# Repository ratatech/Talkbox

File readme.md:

# Ratatech Talkbox

This repository contains mainly the PCB design files for the Ratatech Talkbox unit. 

DESCRIPTION WIP.

## Files

* [datasheets](./datasheets) 	Datasheets of some of the components and schematics used in this project.
* [imgs](./imgs) 				Images used in the design and captures or the 3d models/final pcb.
* [kicad](./kicad) 				Main Kicad project directory. Including schematics and pcb.

---

## License

- **[MIT license](http://opensource.org/licenses/mit-license.php)**

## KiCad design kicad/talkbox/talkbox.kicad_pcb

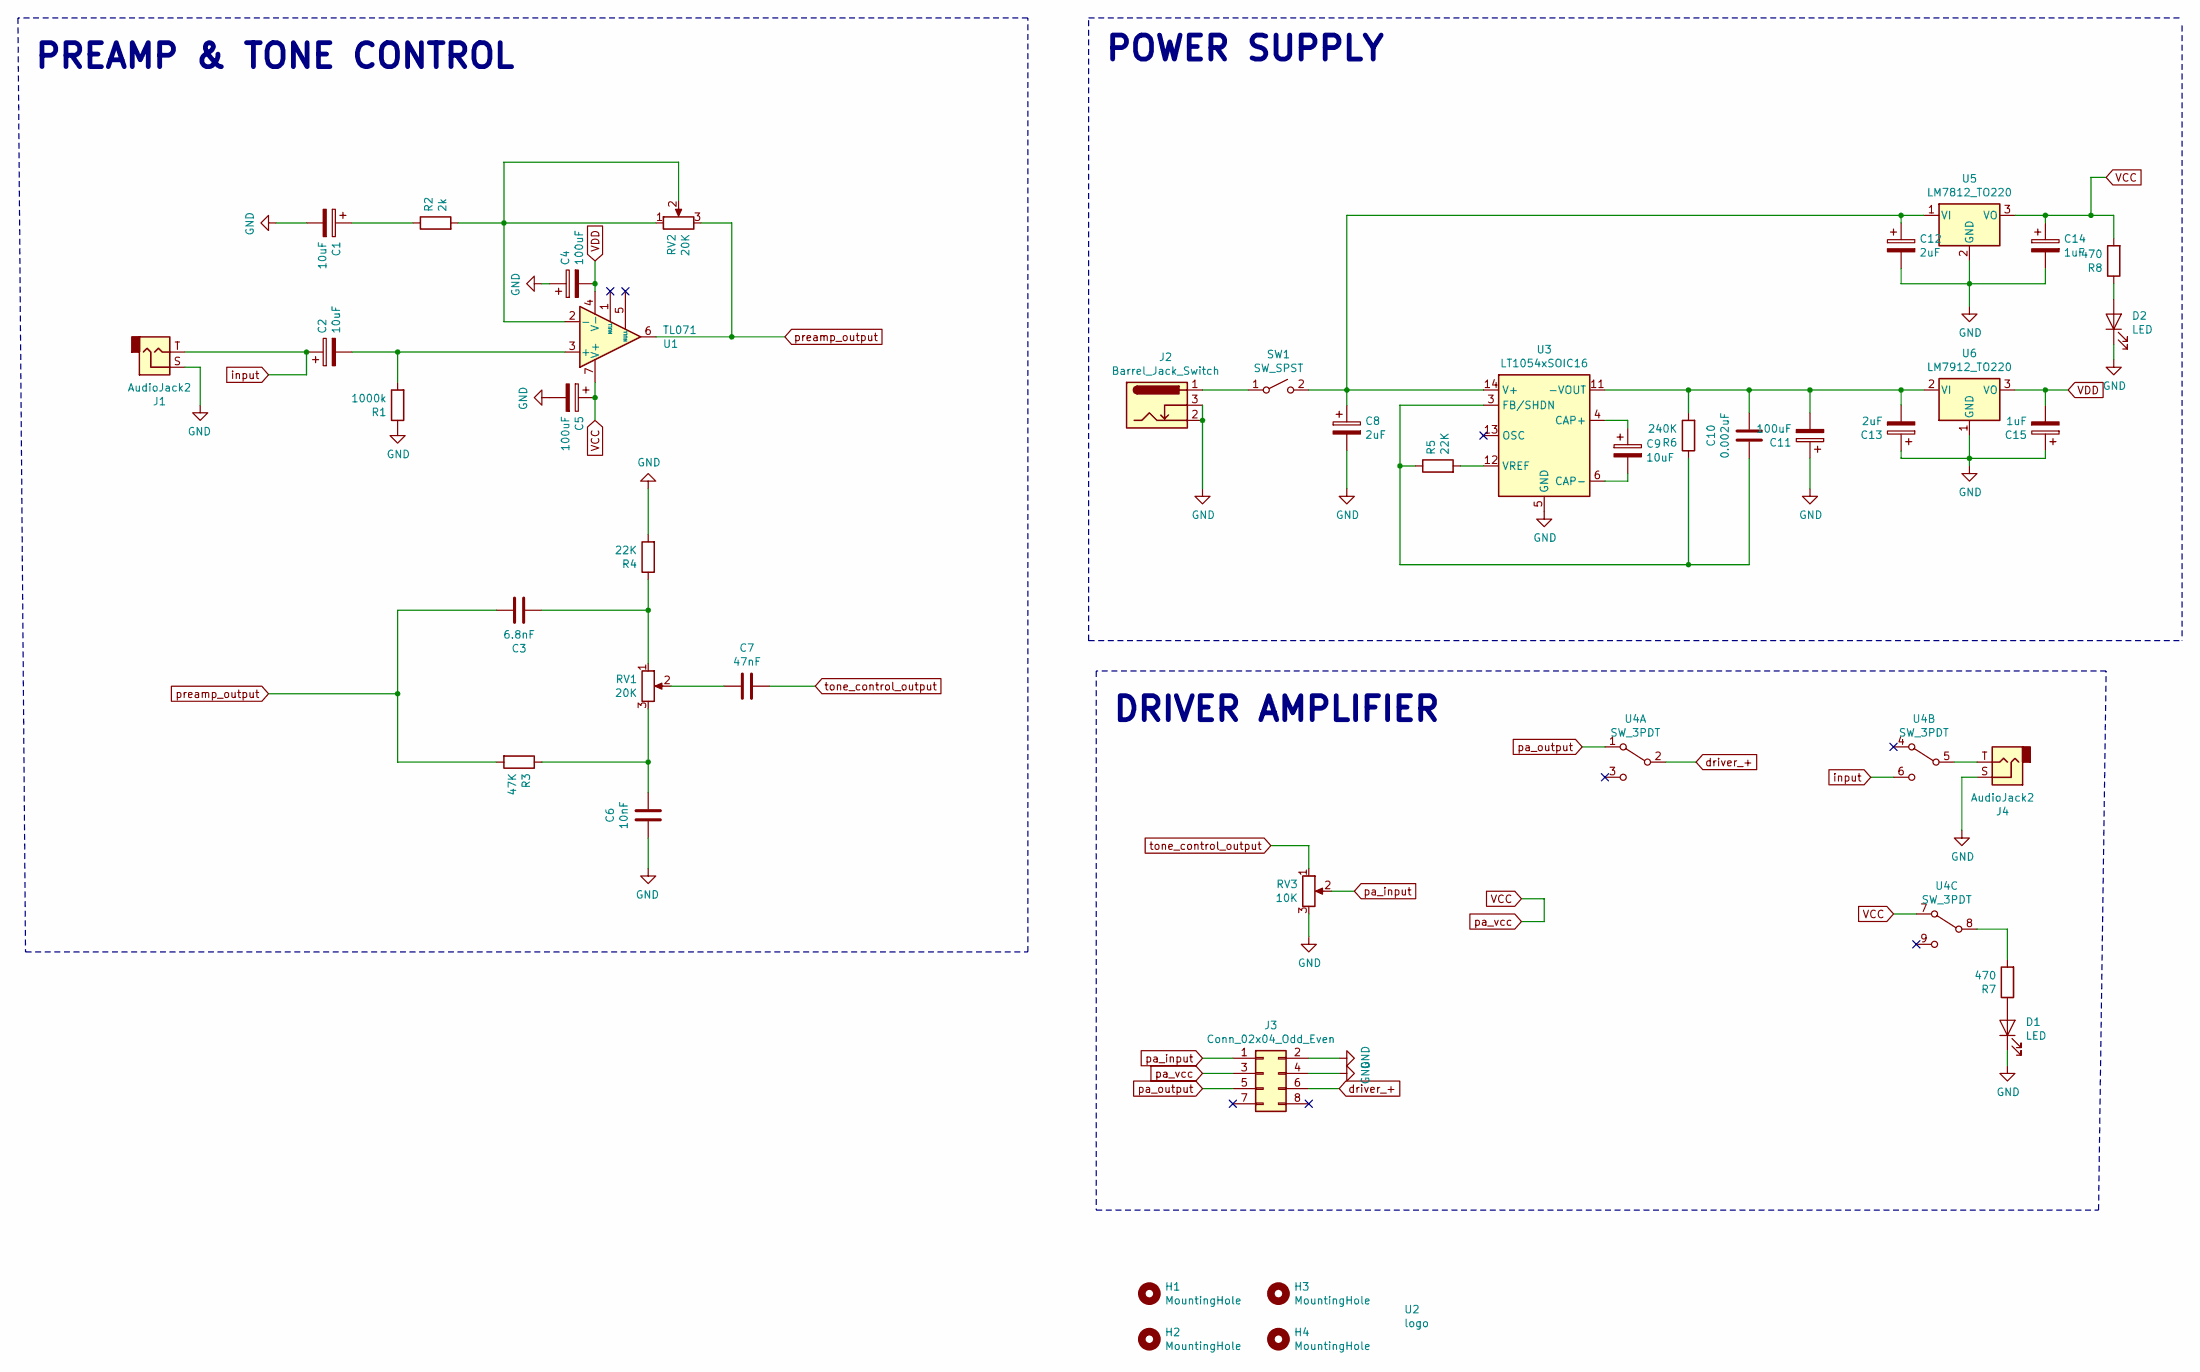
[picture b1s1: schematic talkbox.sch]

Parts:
C1, C2, C9: 10uF; CP_Elec_5x5.3
C3: 6.8nF; C_0603_1608Metric
C4, C5, C11: 100uF; CP_Elec_5x5.3
C6: 10nF; C_0603_1608Metric
C7: 47nF; C_0603_1608Metric
C8, C12, C13: 2uF; CP_Elec_5x5.3
C10: 0.002uF; C_0603_1608Metric
C14, C15: 1uF; CP_Elec_5x5.3
D1, D2: LED; LED_1206_3216Metric
H1, H2, H3, H4: MountingHole; MountingHole_3mm
J1, J4: AudioJack2; Jack_6.35mm_Neutrik_NRJ4HF-1_Horizontal
J2: Barrel_Jack_Switch; BarrelJack_CUI_PJ-102AH_Horizontal
J3: Conn_02x04_Odd_Even; PinHeader_2x04_P2.54mm_Vertical
R1: 1000k; R_0603_1608Metric
R2: 2k; R_0603_1608Metric
R3: 47K; R_0603_1608Metric
R4, R5: 22K; R_0603_1608Metric
R6: 240K; R_0603_1608Metric
R7, R8: 470; R_0603_1608Metric
RV1, RV2: 20K; Potentiometer_Alps_RK09K_Single_Vertical
RV3: 10K; Potentiometer_Alps_RK09K_Single_Vertical
SW1: SW_SPST; SW_CuK_OS102011MA1QN1_SPDT_Angled
U1: TL071; SOIC-8_3.9x4.9mm_P1.27mm
U2: logo; ratatech_bitmap_10x2.8mm
U3: LT1054xSOIC16; SOIC-16W_7.5x10.3mm_P1.27mm
U4: SW_3PDT; PinHeader_2x05_P2.54mm_Vertical
U5: LM7812_TO220; ATPAK-2
U6: LM7912_TO220; ATPAK-2

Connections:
GND: C1.2, C4.1, C5.2, C6.2, C8.2, C11.1, C12.2, C13.1, C14.2, C15.1, D1.1 (K), D2.1 (K), J1.S, J2.2, J2.3, J3.2, J3.4, J4.S, R1.1, R4.2, RV3.3, U3.5 (GND), U5.2 (GND), U6.1 (GND)
unnamed: C1.1, R2.1
unnamed: C2.2, R1.2, U1.3 (+)
unnamed: C3.2, R4.1, RV1.1
unnamed: C6.1, R3.1, RV1.3
unnamed: C7.2, RV1.2
unnamed: C9.1, U3.4 (CAP+)
unnamed: C9.2, U3.6 (CAP-)
unnamed: C10.1, C11.2, C13.2, R6.2, U3.11 (-VOUT), U6.2 (VI)
unnamed: C10.2, R5.1, R6.1, U3.3 (FB/SHDN)
unnamed: C8.1, C12.1, SW1.2 (B), U3.14 (V+), U5.1 (VI)
unnamed: D1.2 (A), R7.1
unnamed: D2.2 (A), R8.1
unnamed: J2.1, SW1.1 (A)
unnamed: J4.T, U4.5 (B)
unnamed: R2.2, RV2.1, RV2.2, U1.2 (-)
unnamed: R5.2, U3.12 (VREF)
unnamed: R7.2, U4.8 (B)
VCC: C5.1, C14.1, J3.3, R8.2, U1.7 (V+), U4.7 (A), U5.3 (VO)
VDD: C4.2, C15.2, U1.4 (V-), U6.3 (VO)
driver_+: J3.6, U4.2 (B)
input: C2.1, J1.T, U4.6 (C)
pa_input: J3.1, RV3.2
pa_output: J3.5, U4.1 (A)
preamp_output: C3.1, R3.2, RV2.3, U1.6
tone_control_output: C7.1, RV3.1

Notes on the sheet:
PREAMP & TONE CONTROL
POWER SUPPLY
DRIVER AMPLIFIER

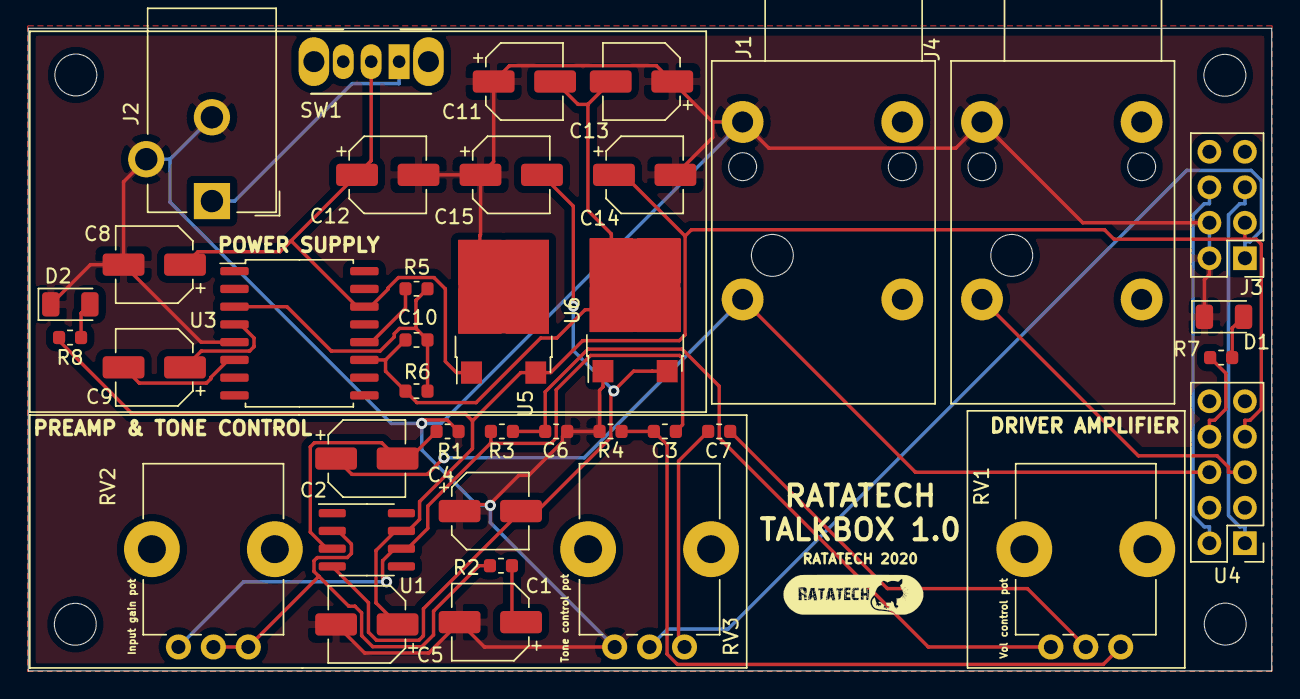
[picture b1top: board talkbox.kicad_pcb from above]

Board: 2 copper layers, 89.0 x 46.0 mm, 43 parts (0 on the bottom side), 26 nets.

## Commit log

2020-05-24 Init repo
2020-05-24 Added kicad libraries and updated pcb
2020-05-24 Added readme file
2020-05-24 Added gitignore
2020-05-24 First time routing
2020-05-25 Added tl072 and preamp stage
2020-05-28 Removed lm386 based power amplifier and adapted tone control
2020-06-07 Changed preamp capacitors to electrolytics
2020-06-07 Re-labeled drive- to GND
2020-06-09 PCB done v1.0. Generated gerbers for fab
2020-06-11 Added partially mouser part numbers
2020-06-14 Finished BOM with mouser part numbers
